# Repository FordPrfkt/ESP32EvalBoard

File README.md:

# ESP32EvalBoard
 Eval Board for ESP32

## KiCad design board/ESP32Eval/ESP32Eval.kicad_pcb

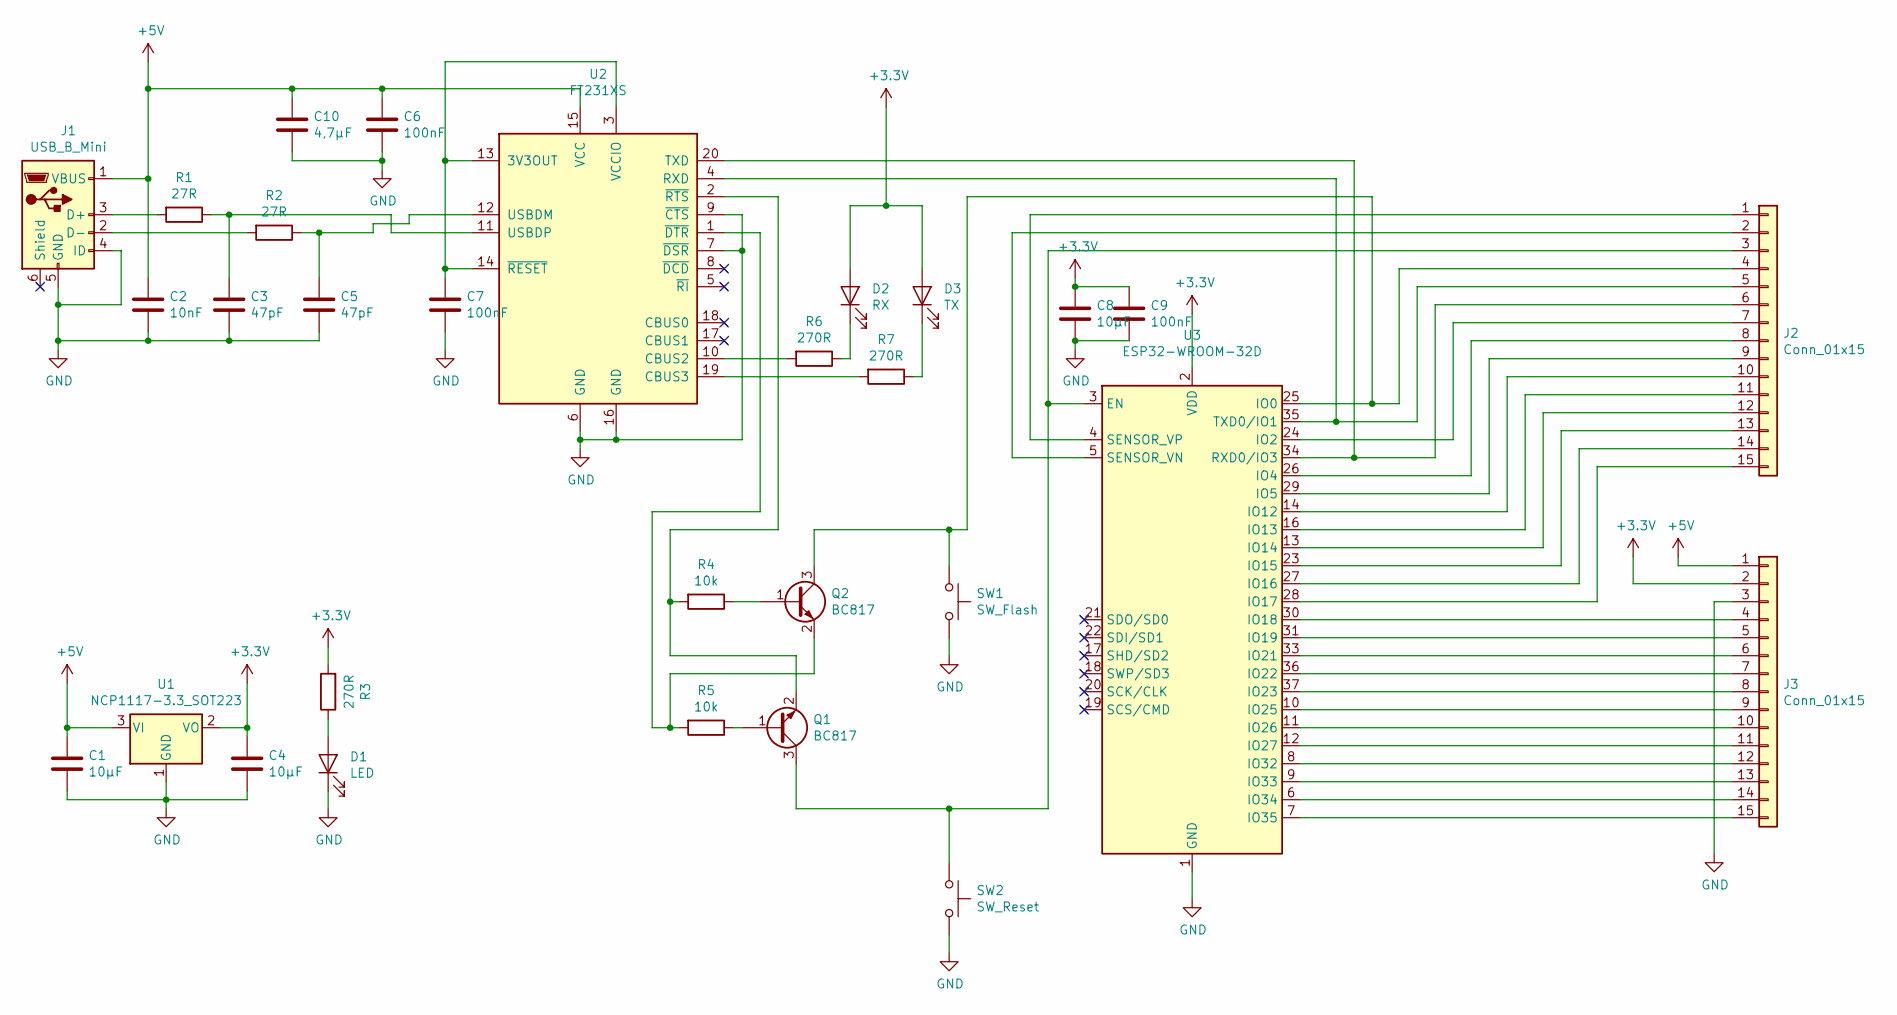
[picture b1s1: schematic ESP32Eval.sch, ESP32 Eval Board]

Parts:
C1, C4, C8: 10µF; C_0805_2012Metric_Pad1.15x1.40mm_HandSolder
C2: 10nF; C_0805_2012Metric_Pad1.15x1.40mm_HandSolder
C3, C5: 47pF; C_0805_2012Metric_Pad1.15x1.40mm_HandSolder
C6, C7, C9: 100nF; C_0805_2012Metric_Pad1.15x1.40mm_HandSolder
C10: 4,7µF; C_0805_2012Metric_Pad1.15x1.40mm_HandSolder
D1: LED; LED_0805_2012Metric_Pad1.15x1.40mm_HandSolder
D2: RX; LED_0805_2012Metric_Pad1.15x1.40mm_HandSolder
D3: TX; LED_0805_2012Metric_Pad1.15x1.40mm_HandSolder
J1: USB_B_Mini; USB_Mini-B_Lumberg_2486_01_Horizontal
J2, J3: Conn_01x15; PinHeader_1x15_P2.54mm_Vertical
Q1, Q2: BC817; SOT-23
R1, R2: 27R; R_0805_2012Metric_Pad1.15x1.40mm_HandSolder
R3, R6, R7: 270R; R_0805_2012Metric_Pad1.15x1.40mm_HandSolder
R4, R5: 10k; R_0805_2012Metric_Pad1.15x1.40mm_HandSolder
SW1: SW_Flash; SW_SPST_B3S-1000
SW2: SW_Reset; SW_SPST_B3S-1000
U1: NCP1117-3.3_SOT223; SOT-223-3_TabPin2
U2: FT231XS; SSOP-20_3.9x8.7mm_P0.635mm
U3: ESP32-WROOM-32D; ESP32-WROOM-32

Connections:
+3V3: C4.1, C8.1, C9.1, D2.2 (A), D3.2 (A), J3.2, R3.2, U1.2 (VO), U3.2 (VDD)
+5V: C1.1, C2.1, C6.1, C10.1, J1.1 (VBUS), J3.1, U1.3 (VI), U2.15 (VCC)
GND: C1.2, C2.2, C3.2, C4.2, C5.2, C6.2, C7.2, C8.2, C9.2, C10.2, D1.1 (K), J1.4 (ID), J1.5 (GND), J3.3, SW1.2, SW2.2, U1.1 (GND), U2.6 (GND), U2.7 (~DSR), U2.9 (~CTS), U2.16 (GND), U3.1 (GND), U3.15 (GND), U3.38 (GND); also elsewhere on the board
unnamed: C3.1, R1.1, U2.11 (USBDP)
unnamed: C5.1, R2.1, U2.12 (USBDM)
unnamed: C7.1, U2.3 (VCCIO), U2.13 (3V3OUT), U2.14 (~RESET)
unnamed 6: J1.6 (Shield); also elsewhere on the board
unnamed: D1.2 (A), R3.1
unnamed: D2.1 (K), R6.1
unnamed: D3.1 (K), R7.1
unnamed: J1.2 (D-), R2.2
unnamed: J1.3 (D+), R1.2
unnamed: J2.1, U3.4 (SENSOR_VP)
unnamed: J2.2, U3.5 (SENSOR_VN)
unnamed: J2.3, Q1.3 (C), SW2.1, U3.3 (EN)
unnamed: J2.4, Q2.3 (C), SW1.1, U3.25 (IO0)
unnamed: J2.5, U2.4 (RXD), U3.35 (TXD0/IO1)
unnamed: J2.6, U2.20 (TXD), U3.34 (RXD0/IO3)
unnamed: J2.7, U3.24 (IO2)
unnamed: J2.8, U3.26 (IO4)
unnamed: J2.9, U3.29 (IO5)
unnamed: J2.10, U3.14 (IO12)
unnamed: J2.11, U3.16 (IO13)
unnamed: J2.12, U3.13 (IO14)
unnamed: J2.13, U3.23 (IO15)
unnamed: J2.14, U3.27 (IO16)
unnamed: J2.15, U3.28 (IO17)
unnamed: J3.4, U3.30 (IO18)
unnamed: J3.5, U3.31 (IO19)
unnamed: J3.6, U3.33 (IO21)
unnamed: J3.7, U3.36 (IO22)
unnamed: J3.8, U3.37 (IO23)
unnamed: J3.9, U3.10 (IO25)
unnamed: J3.10, U3.11 (IO26)
unnamed: J3.11, U3.12 (IO27)
unnamed: J3.12, U3.8 (IO32)
unnamed: J3.13, U3.9 (IO33)
unnamed: J3.14, U3.6 (IO34)
unnamed: J3.15, U3.7 (IO35)
unnamed: Q1.1 (B), R5.1
unnamed: Q1.2 (E), R4.2, U2.2 (~RTS)
unnamed: Q2.1 (B), R4.1
unnamed: Q2.2 (E), R5.2, U2.1 (~DTR)
unnamed: R6.2, U2.10 (CBUS2)
unnamed: R7.2, U2.19 (CBUS3)

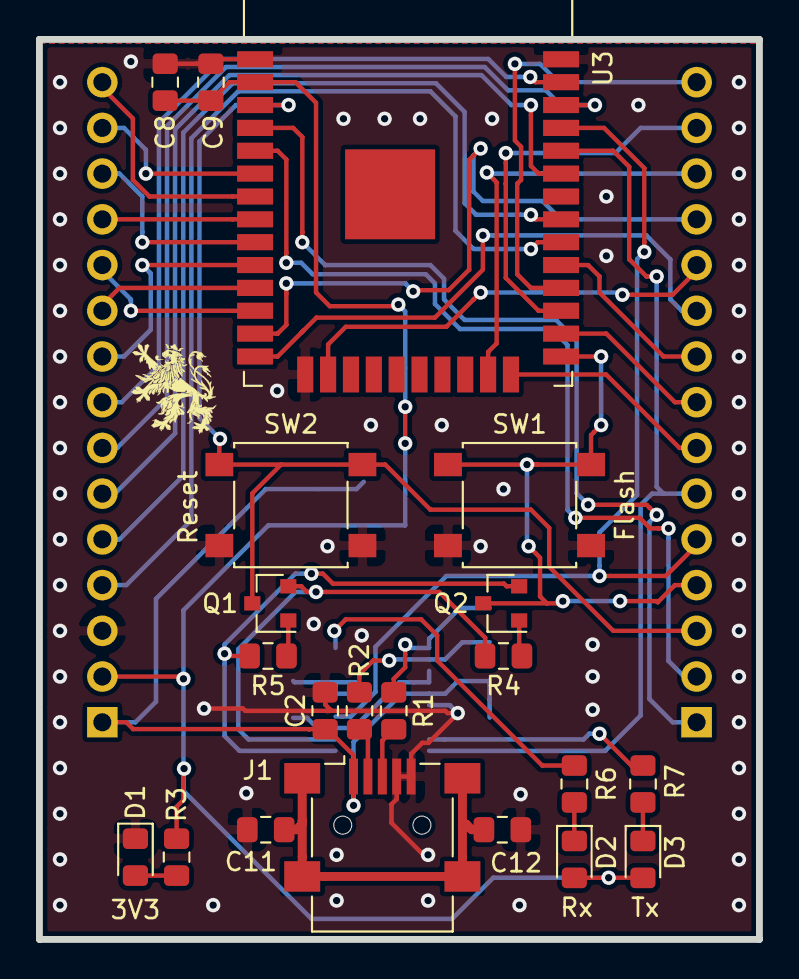
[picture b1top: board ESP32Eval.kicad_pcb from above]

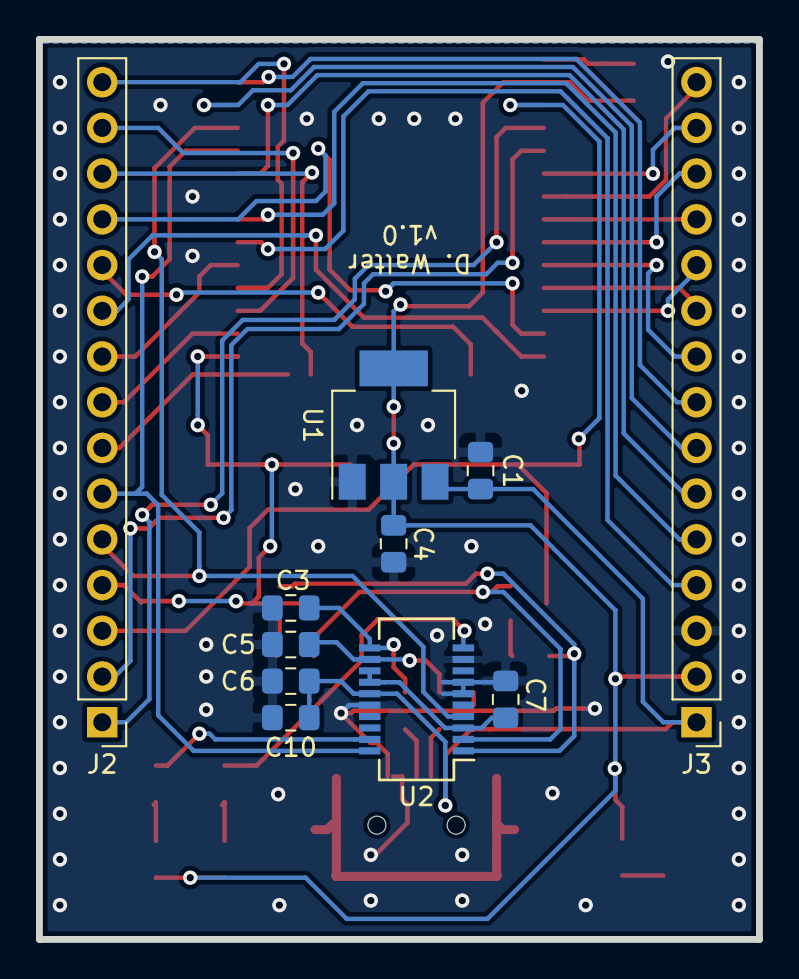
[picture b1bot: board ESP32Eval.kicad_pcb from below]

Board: 2 copper layers, 40.0 x 50.0 mm, 32 parts (11 on the bottom side), 45 nets.

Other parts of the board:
C11, C12: 10nF; C_0805_2012Metric_Pad1.15x1.40mm_HandSolder

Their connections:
GND: C11.2, C12.2; also elsewhere on the board
unnamed 6: C11.1, C12.1; also elsewhere on the board

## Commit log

2019-09-21 Initial commit
    Board created
2019-09-22 Layout changes, added missing filter cap
2019-12-15 Connected USB Shield trough Capacitors
